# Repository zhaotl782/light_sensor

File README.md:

# light_sensor
Light Sensor schematic files, built in KiCad.

3D View

Schematic

Layout in KiCad PCB Editor

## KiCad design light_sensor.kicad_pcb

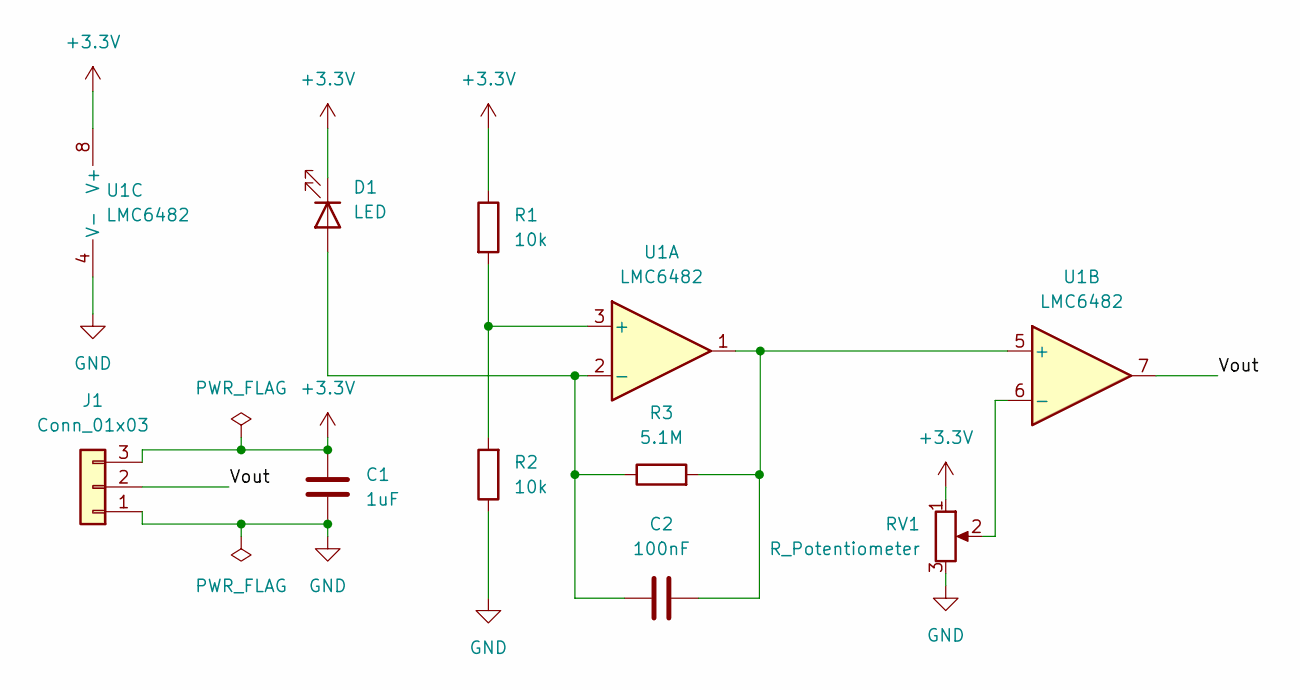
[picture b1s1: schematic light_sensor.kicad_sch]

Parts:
C1: 1uF; C_0805_2012Metric
C2: 100nF; C_0805_2012Metric
D1: LED; LED_D5.0mm
J1: Conn_01x03; PinHeader_1x03_P2.54mm_Vertical
R1, R2: 10k; R_Axial_DIN0204_L3.6mm_D1.6mm_P5.08mm_Horizontal
R3: 5.1M; R_Axial_DIN0204_L3.6mm_D1.6mm_P5.08mm_Horizontal
RV1: R_Potentiometer; Potentiometer_Vishay_T7-YA_Single_Vertical
U1: LMC6482; DIP-8-16_W7.62mm

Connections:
+3.3V: C1.1, D1.1 (K), J1.3, R1.1, RV1.1, U1.8 (V+)
/Vout: J1.2, U1.7
GND: C1.2, J1.1, R2.1, RV1.3, U1.4 (V-)
unnamed: C2.1, D1.2 (A), R3.1, U1.2 (-)
unnamed: R1.2, R2.2, U1.3 (+)
unnamed: C2.2, R3.2, U1.1, U1.5 (+)
unnamed: RV1.2, U1.6 (-)

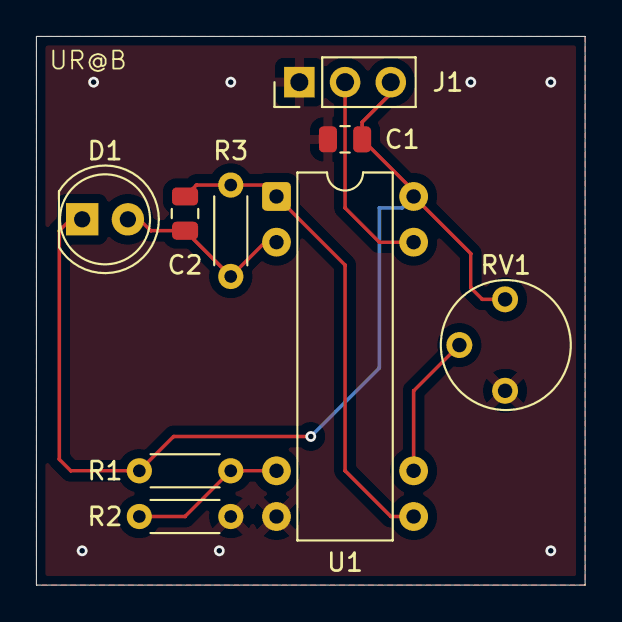
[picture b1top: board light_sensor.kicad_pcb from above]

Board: 2 copper layers, 30.5 x 30.5 mm, 9 parts (0 on the bottom side), 7 nets.

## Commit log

2026-03-13 KiCad files for light sensor
